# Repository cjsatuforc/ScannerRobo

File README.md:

# Project ScannerLaser

Developing a small laser scanner with a single CMD camera and two lasers. 
One of these lasers is coupled with a small DC motor and the controller of the motor is being implemented in a small arduino nano pro board.

Everything communicating with a PC via USB serial

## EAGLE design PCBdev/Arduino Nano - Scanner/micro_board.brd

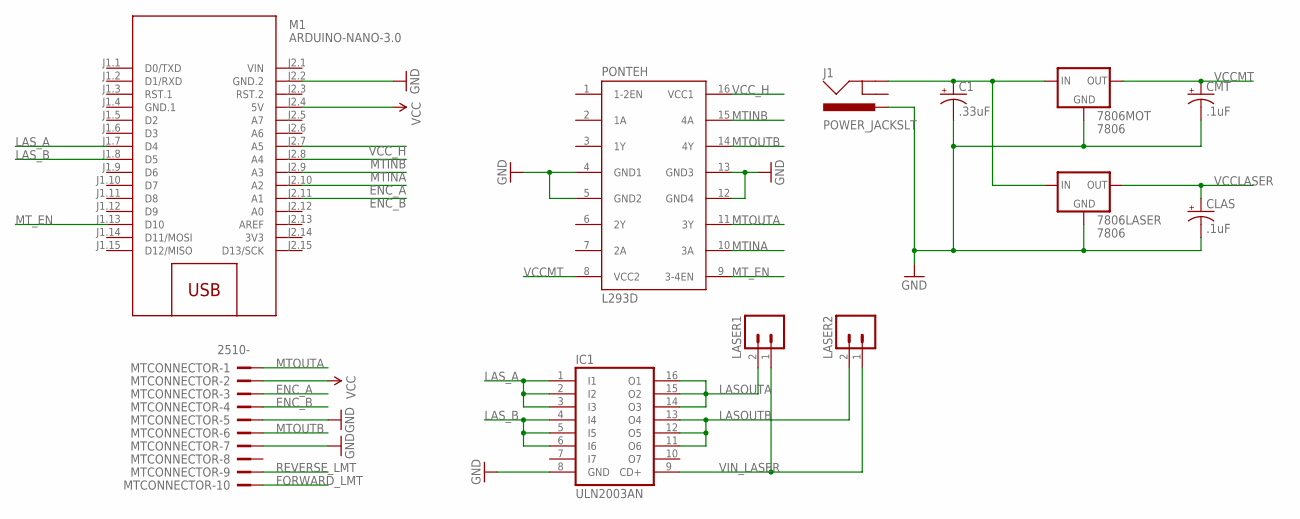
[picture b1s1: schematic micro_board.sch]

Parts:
7806LASER, 7806MOT: 7806; TO220-IGO
C1: .33uF; CPOL-RADIAL-100UF-25V
CLAS: .1uF; CPOL-RADIAL-100UF-25V
CMT: .1uF; CPOL-RADIAL-100UF-25V
IC1: ULN2003AN; DIL16
J1: POWER_JACKSLT; POWER_JACK_SLOT
LASER1, LASER2: M02POLAR; MOLEX-1X2
M1: ARDUINO-NANO-3.0
MTCONNECTOR: 2510-; PAK100/2500-10
PONTEH: L293D; DIL16

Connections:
3V3: M1.J2.14 (3V3)
ENC_A: M1.J2.10 (A2), MTCONNECTOR.3
ENC_B: M1.J2.11 (A1), MTCONNECTOR.4
FORWARD_LMT: MTCONNECTOR.10
GND: 7806LASER.GND, 7806MOT.GND, C1.2 (-), CLAS.2 (-), CMT.2 (-), IC1.8 (GND), J1.PWR, M1.J2.2 (GND.2), MTCONNECTOR.5, MTCONNECTOR.7, PONTEH.4 (GND1), PONTEH.5 (GND2), PONTEH.12 (GND4), PONTEH.13 (GND3)
GND.1: M1.J1.4 (GND.1)
LASOUTA: IC1.14 (O3), IC1.15 (O2), IC1.16 (O1), LASER1.2
LASOUTB: IC1.11 (O6), IC1.12 (O5), IC1.13 (O4), LASER2.2
LAS_A: IC1.1 (I1), IC1.2 (I2), IC1.3 (I3), M1.J1.7 (D4)
LAS_B: IC1.4 (I4), IC1.5 (I5), IC1.6 (I6), M1.J1.8 (D5)
MTINA: M1.J2.9 (A3), PONTEH.10 (3A)
MTINB: M1.J2.8 (A4), PONTEH.15 (4A)
MTOUTA: MTCONNECTOR.1, PONTEH.11 (3Y)
MTOUTB: MTCONNECTOR.6, PONTEH.14 (4Y)
MT_EN: M1.J1.13 (D10), PONTEH.9 (3-4EN)
REVERSE_LMT: MTCONNECTOR.9
SRCIN: 7806LASER.IN, 7806MOT.IN, C1.1 (+), J1.GND@2 (GND)
VCC: M1.J2.4 (5V), MTCONNECTOR.2
VCCLASER: 7806LASER.OUT, CLAS.1 (+)
VCCMT: 7806MOT.OUT, CMT.1 (+), PONTEH.8 (VCC2)
VCC_H: M1.J2.7 (A5), PONTEH.16 (VCC1)
VIN: M1.J2.1 (VIN)
VIN_LASER: IC1.9 (CD+), LASER1.1, LASER2.1

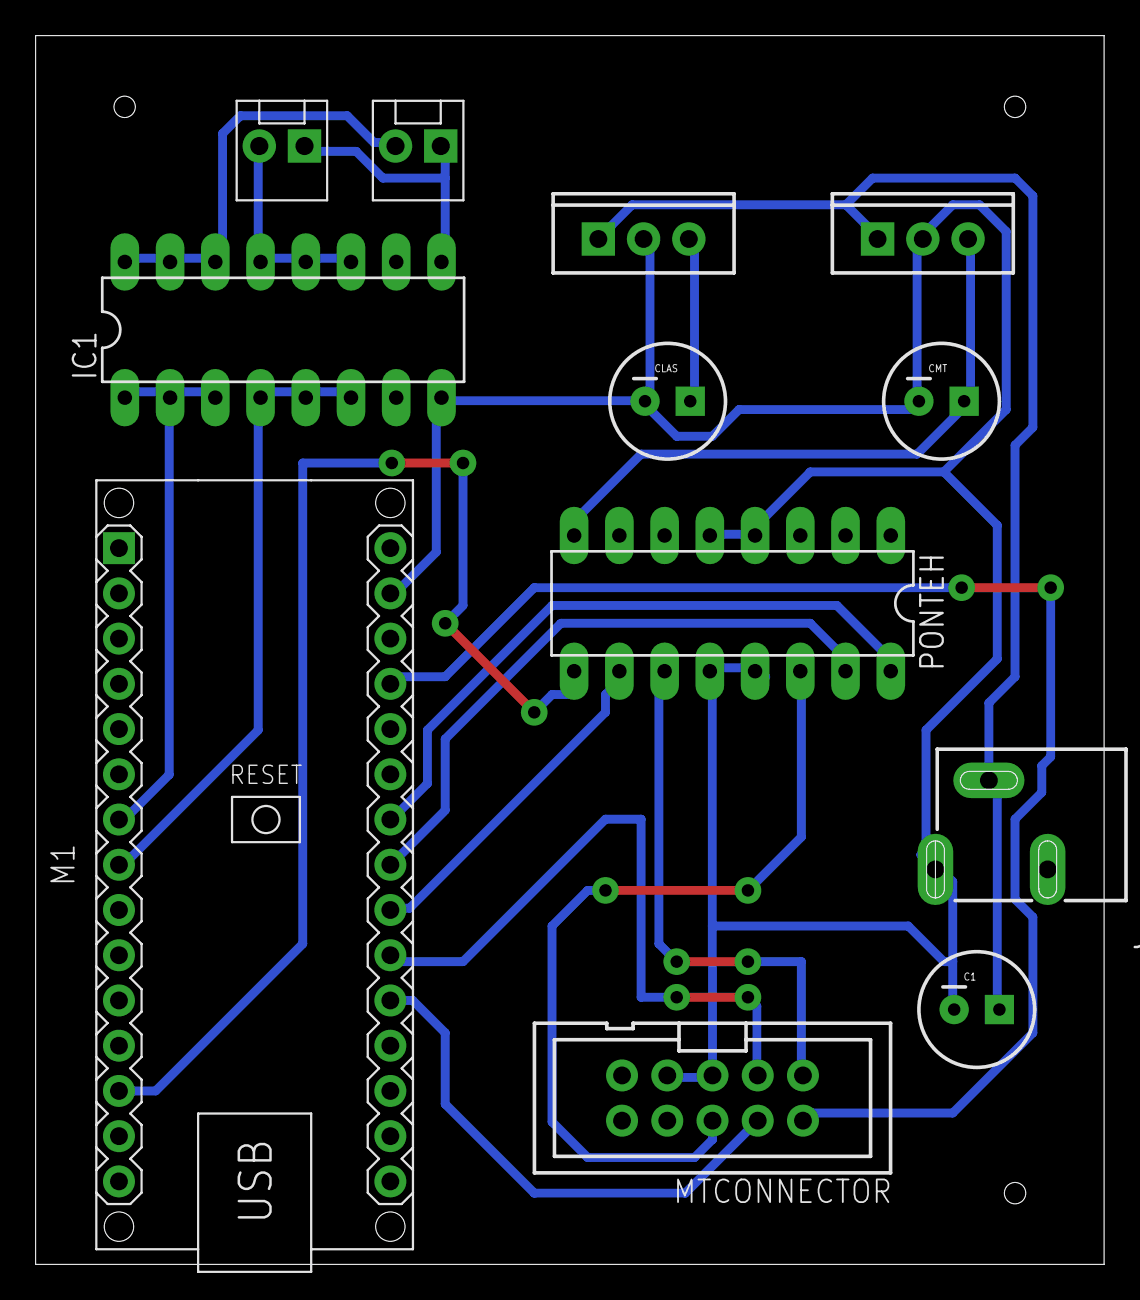
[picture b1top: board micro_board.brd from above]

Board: 2 copper layers, 60.0 x 69.0 mm, 12 parts (0 on the bottom side), 18 nets.

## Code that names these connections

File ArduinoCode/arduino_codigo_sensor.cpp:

/*
 * arduino_codigo_sensor.cpp
 *
 *  Created on: Aug 4, 2016
 *      Author: jesseh
 */


class SerialCommunication
{

private:
  String str = "";
  char c;
public:

  void init(int baud = 9600)
  {
    Serial.begin(baud);
    Serial.println("Starting Connection...");
    for(;;)
    {
      if(getString() == "finatec")
        break;
    }
    Serial.println("Connection Done!");
  }

  bool status()
  {
    return Serial.available();
  }

  String getString()
  {
    str = "";
    c = ' ';

    for(;Serial.available() > 0;)
    {
        c = Serial.read();
        if(c != '\n')
          str.concat(c);
        else
          break;
        delay(5);
    }
    //Serial.print("Received: ");
    //Serial.println(str);
    return str;
  }

  void writeString(String str)
  {
    Serial.println(str);
  }

  void writeStringwn(String str)
  {
    Serial.print(str);
  }

  float getFloat()
  {
    getString();
    return str.toFloat();
  }

  void writeFloat(float f)
  {
    Serial.print(f,3);
  }

  int getInt()
  {
    getString();
    return str.toInt();
  }
};

//PARA O NANO
class DCMotor
{
private:
  //Pinos da ponte H
  int _pinVCC, _pinMOT_IN1, _pinMOT_IN2, _pinMOT_PWM;

  //Carcateristicas de giro
  bool _sent_gir; //Sentido de giro (anti-horario)
  bool _is_running;
  int _speedPWM; //Largura do pulso do PWM
  short _defaultSpeedPWM;

public:
  DCMotor(int pinVCC, int pinMOTIN1, int pinMOTIN2, int pinMOTPWM, short defaultPWMSpeed=6, int pwmFrequencyScaler=1024)
  {
    setPin(pinVCC, pinMOTIN1, pinMOTIN2, pinMOTPWM);
    _sent_gir = true;
    _speedPWM = 0;
    _is_running = 0;
    stopMotor();
    setDefaultSpeedPWM(defaultPWMSpeed);
    setPWMfrequency(pwmFrequencyScaler);
  }

  void setPin(int pinVCC, int pinMOTIN1, int pinMOTIN2, int pinMOTPWM)
  {
    _pinVCC = pinVCC;
    _pinMOT_IN1 = pinMOTIN1;
    _pinMOT_IN2 = pinMOTIN2;
    _pinMOT_PWM = pinMOTPWM;
    pinMode(_pinVCC, OUTPUT);
    pinMode(_pinMOT_IN1, OUTPUT);
    pinMode(_pinMOT_IN2, OUTPUT);
    pinMode(_pinMOT_PWM, OUTPUT);
  }

  void setSentidoGiro(bool is_antihorario)
  {
    analogWrite(_pinMOT_PWM, 0);
    _sent_gir = is_antihorario;
    digitalWrite(_pinMOT_IN1, (!_sent_gir)&&(_is_running));
    digitalWrite(_pinMOT_IN2, (_sent_gir)&&(_is_running));
    analogWrite(_pinMOT_PWM, _speedPWM*(_is_running? 1 : 0));
  }

  void setPWMfrequency(int prescaler)
  {
    //Seta o prescalling do clock para o timer que é definido pelo pino
    byte scaler;
    switch(prescaler)
    {
    case 1:
      scaler = 0x01;
      break;
    case 8:
      scaler = 0x02;
      break;
    case 64:
      scaler = 0x03;
      break;
    case 256:
      scaler = 0x04;
      break;
    case 1024:
      scaler = 0x05;
      break;
    default:
      scaler = 0x03;
      break;
    }


    TCCR1B = (TCCR1B & 0b11111000) | scaler;

    //MICRO PRO
    //Evitar usar os pinos 3,9, 10
    //Porque a mudanca do prescaler do clock pode alterar outras funcoes
    //que usam os registradores de time comparison do ATMEGA32U4
//    if(pin==3) //Pino OC0B
//    {
//      TCCR0B = (TCCR0B & 0b11111000) | scaler;
//    }
//    else if(pin==5)//Pino OC3A
//    {
//      TCCR3B = (TCCR3B & 0b11111000) | scaler;
//    }
//    else if(pin==6)//Pino OC4D
//    {
//      TCCR4B = (TCCR4B & 0b11111000) | scaler;
//    }
//    else if(pin==9||pin==10)//Pino OC1A e OC1B
//    {
//      TCCR1B = (TCCR1B & 0b11111000) | scaler;
//    }
  }

  void setDefaultSpeedPWM(short newDefaultSpeed)
  {
    _defaultSpeedPWM = newDefaultSpeed;
  }

  void setSpeedPWM()
  {
    _speedPWM = _defaultSpeedPWM;
    analogWrite(_pinMOT_PWM, _speedPWM*(_is_running? 1 : 0));
  }

  void setSpeedPWM(short speedPWM)
  {
    _speedPWM = speedPWM;
    analogWrite(_pinMOT_PWM, _speedPWM*(_is_running? 1 : 0));
  }

  void turnOnHBridge()
  {
    digitalWrite(_pinVCC, HIGH);
  }

  void turnOffHBridge()
  {
    _is_running = false;
    analogWrite(_pinMOT_PWM, 0);
    digitalWrite(_pinMOT_IN1, LOW);
    digitalWrite(_pinMOT_IN2, LOW);
    digitalWrite(_pinVCC, LOW);
  }

  void runMotor()
  {
    turnOnHBridge();
    _is_running = true;
    analogWrite(_pinMOT_PWM, _speedPWM*(_is_running? 1 : 0));
    digitalWrite(_pinMOT_IN1, (_sent_gir)&&(_is_running));
    digitalWrite(_pinMOT_IN2, (!_sent_gir)&&(_is_running));
  }

  void stopMotor()
  {
    _is_running = false;
    analogWrite(_pinMOT_PWM, 0);
    digitalWrite(_pinMOT_IN1, LOW);
    digitalWrite(_pinMOT_IN2, LOW);
  }

};

void runCommand(DCMotor motor_, SerialCommunication usb, String cmd, int las_a, int las_b)
{
    if (cmd=="ligar laser fixo") {
      digitalWrite(las_b, HIGH);
      usb.writeString("OK!");
    }
    else if (cmd == "ligar laser movel") {
      digitalWrite(las_a, HIGH);
      usb.writeString("OK!");
    }
    else if (cmd== "desligar laser fixo") {
      digitalWrite(las_b, LOW);
      usb.writeString("OK!");
    }
    else if (cmd== "desligar laser movel") {
      digitalWrite(las_a, LOW);
      usb.writeString("OK!");
    }
    else if (cmd== "parar motor") {
      motor_.stopMotor();
      motor_.turnOffHBridge();
      usb.writeString("OK");
    }
    else if (cmd== "ligar motor horario") {
      motor_.turnOnHBridge();
      motor_.setSentidoGiro(false);
      motor_.setSpeedPWM();
      motor_.runMotor();
      usb.writeString("OK!");
    }
    else if ("ligar motor antihorario") {
      motor_.turnOnHBridge();
      motor_.setSentidoGiro(true);
      motor_.setSpeedPWM();
      motor_.runMotor();
      usb.writeString("OK!");
    }
    else if (cmd== "ligar motor horario rapido") {
      motor_.turnOnHBridge();
      motor_.setSentidoGiro(false);
      motor_.setSpeedPWM(25);
      motor_.runMotor();
      usb.writeString("OK!");
    }
    else if (cmd== "ligar motor antihorario rapido") {
      motor_.turnOnHBridge();
      motor_.setSentidoGiro(true);
      motor_.setSpeedPWM(25);
      motor_.runMotor();
      usb.writeString("OK!");
    }
  }


//pinos
//lasers
int las_a = 4;
int las_b = 5;
int mot_in1 = 18;
int mot_in2 = 17;
int mot_pwm = 10; //SEMPRE USAR O 10 no nano
int mot_vcc = 19;
int enc_a = 16;
int enc_b = 15;
DCMotor motor(mot_vcc, mot_in1, mot_in2, mot_pwm);
SerialCommunication usb_com;

void setup()
{
  analogWrite(mot_pwm, 0);
  Serial.begin(9600);

  motor.turnOffHBridge();
  motor.turnOnHBridge();


  usb_com.init();
  digitalWrite(mot_vcc, HIGH);

  //Setup dos Lasers
  pinMode(las_a, OUTPUT);
  pinMode(las_b, OUTPUT);
  digitalWrite(las_a, LOW);
  digitalWrite(las_b, LOW);
}

String command;
void loop()
{

  //usb_com.writeString("Waiting Command!");
  if(usb_com.status() > 0)
     command = usb_com.getString();
  else
    command = "";

  if(command .length() == 0)
    return;

  usb_com.writeStringwn("Command: ");
  usb_com.writeString(command);

  runCommand(motor, usb_com, command, las_a, las_b);
}

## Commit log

2016-11-04 Adicionando o PCB e codigos funcionando
2016-11-08 nano_dxf
2016-11-09 modelos
2016-11-16 Adding a 3D model of the box for the sensor
    Solid Works model of the box
2016-11-16 Changing folder location of the box model
2016-11-25 Alterando o codigo do arduino para executar uma velocidade de PWM default.
2016-11-28 Add tampa lateral furada com furo
    Ainda deve possuir um furo para as porcas.
2016-12-10 Removing unused files
2016-12-10 Adding a fast command to motors
2016-12-10 Adding a modified version of the robot code
2016-12-11 Tampa Lateral Furada para o HUB
2016-12-11 Adding tampas com HUB
2016-12-11 Back up from the code being used in the scanner

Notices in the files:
parts and their libraries:
SparkFun-Boards: Licensing: Creative Commons ShareAlike 4.0 International - https://creativecommons.org/licenses/by-sa/4.0
diy-modules: Released under the Creative Commons Attribution 4.0 International License: http://creativecommons.org/licenses/by/4.0
